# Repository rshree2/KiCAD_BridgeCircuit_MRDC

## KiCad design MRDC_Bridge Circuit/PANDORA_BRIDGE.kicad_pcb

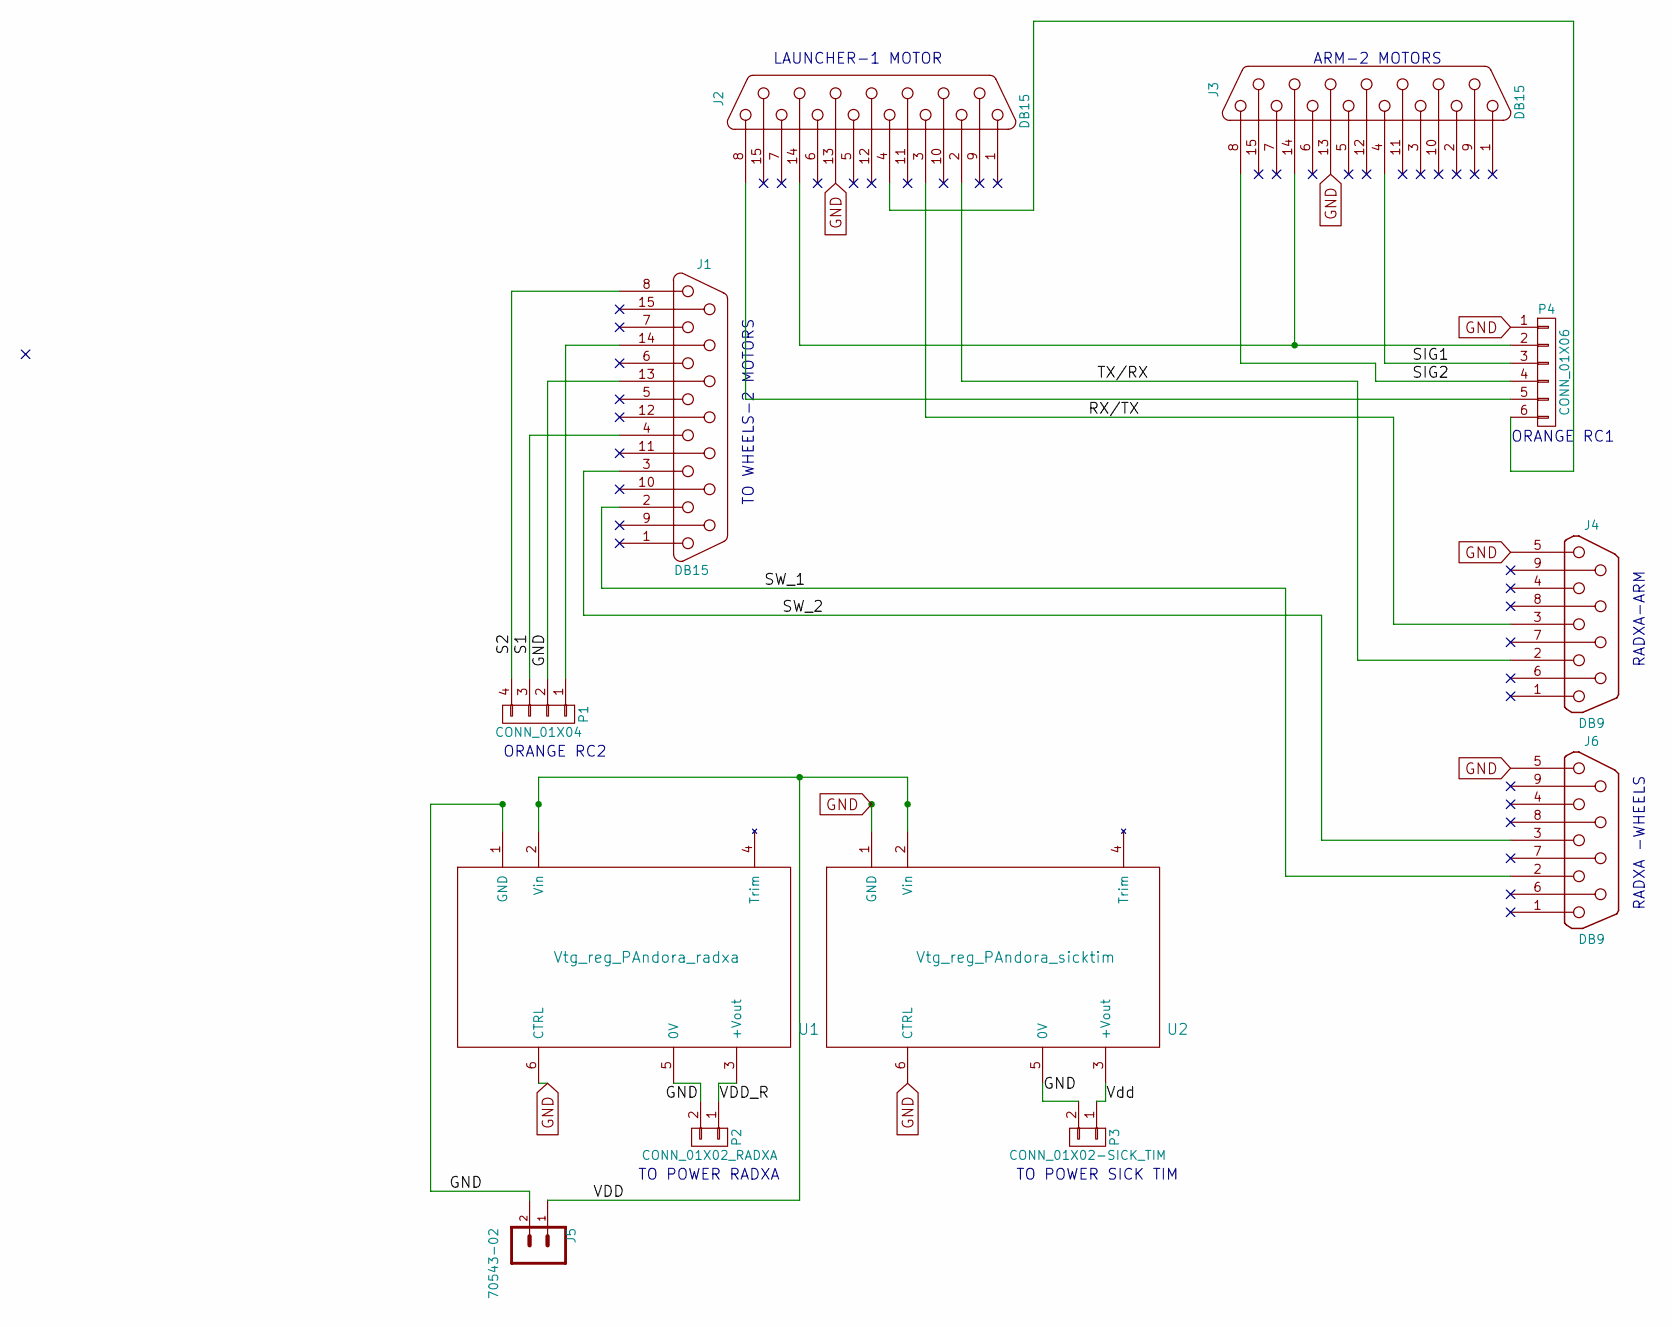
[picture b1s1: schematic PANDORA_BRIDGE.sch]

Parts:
J1, J2, J3: DB15; DB15FD
J4, J6: DB9; DB9FD
J5: 70543-02; MOLEX0428202213
P1: CONN_01X04; Pin_Header_Straight_1x04
P2: CONN_01X02_RADXA; Pin_Header_Straight_1x02
P3: CONN_01X02-SICK_TIM; Pin_Header_Straight_1x02
P4: CONN_01X06; Pin_Header_Straight_1x06
U1: Vtg_reg_PAndora_radxa; vtg_reg_Pandora_sicktim
U2: Vtg_reg_PAndora_sicktim; vtg_reg_Pandora_sicktim

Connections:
/RX/TX: J2.3, J4.3
/S1: J1.4, P1.3
/S2: J1.8, P1.4
/SIG1: J3.4, P4.3
/SIG2: J3.8, P4.4
/SW_1: J1.2, J6.2
/SW_2: J1.3, J6.3
/TX/RX: J2.2, J4.2
/VDD: J5.1, P3.1, U1.2 (Vin), U2.2 (Vin), U2.3 (+Vout)
/VDD_R: P2.1, U1.3 (+Vout)
GND: J1.13, J2.13, J3.13, J4.5, J5.2, J6.5, P1.2, P3.2, P4.1, U1.1 (GND), U1.6 (CTRL), U2.1 (GND), U2.5 (0V), U2.6 (CTRL)
unnamed: J1.14, P1.1
unnamed: J2.4, P4.6
unnamed: J2.8, P4.5
unnamed: J2.14, J3.14, P4.2
unnamed: P2.2, U1.5 (0V)

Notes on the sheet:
ARM-2 MOTORS
LAUNCHER-1 MOTOR
TO WHEELS-2 MOTORS
ORANGE RC1
ORANGE RC2
TO POWER RADXA
TO POWER SICK TIM
RADXA -WHEELS
RADXA-ARM

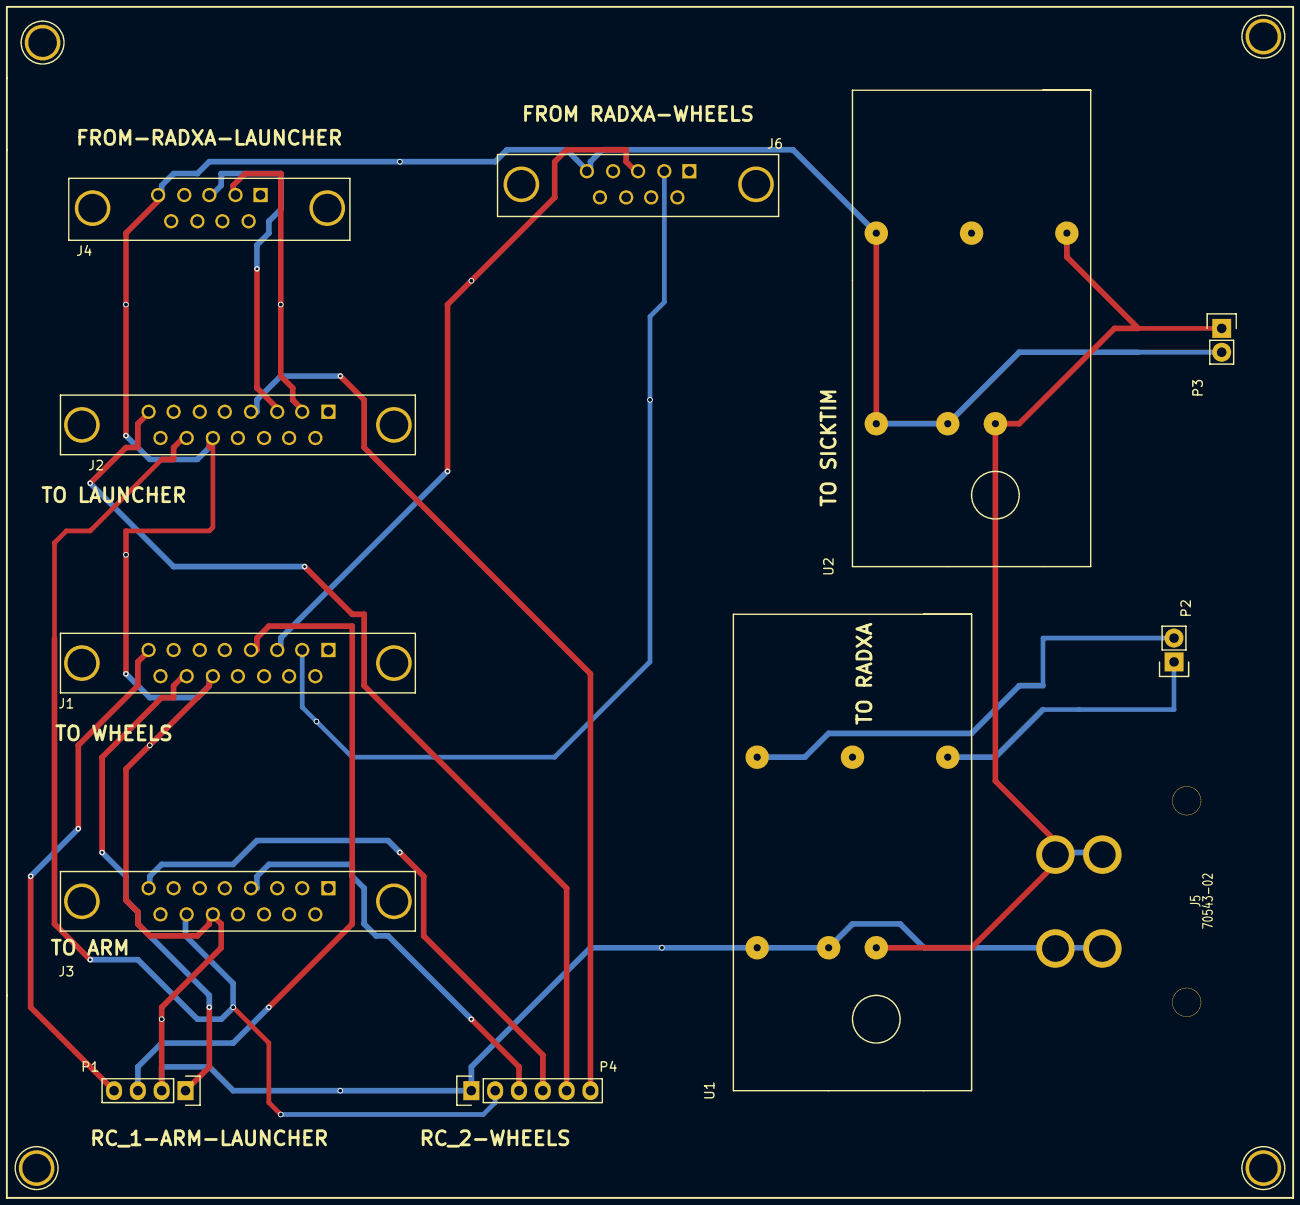
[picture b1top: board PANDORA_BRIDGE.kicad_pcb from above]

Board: 2 copper layers, 16 parts (0 on the bottom side), 16 nets.

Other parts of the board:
P**: 1pin
P**#2, P**#3, P**#4: 1pin

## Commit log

2017-10-18 All files for The MRDC Bridge Circuit
